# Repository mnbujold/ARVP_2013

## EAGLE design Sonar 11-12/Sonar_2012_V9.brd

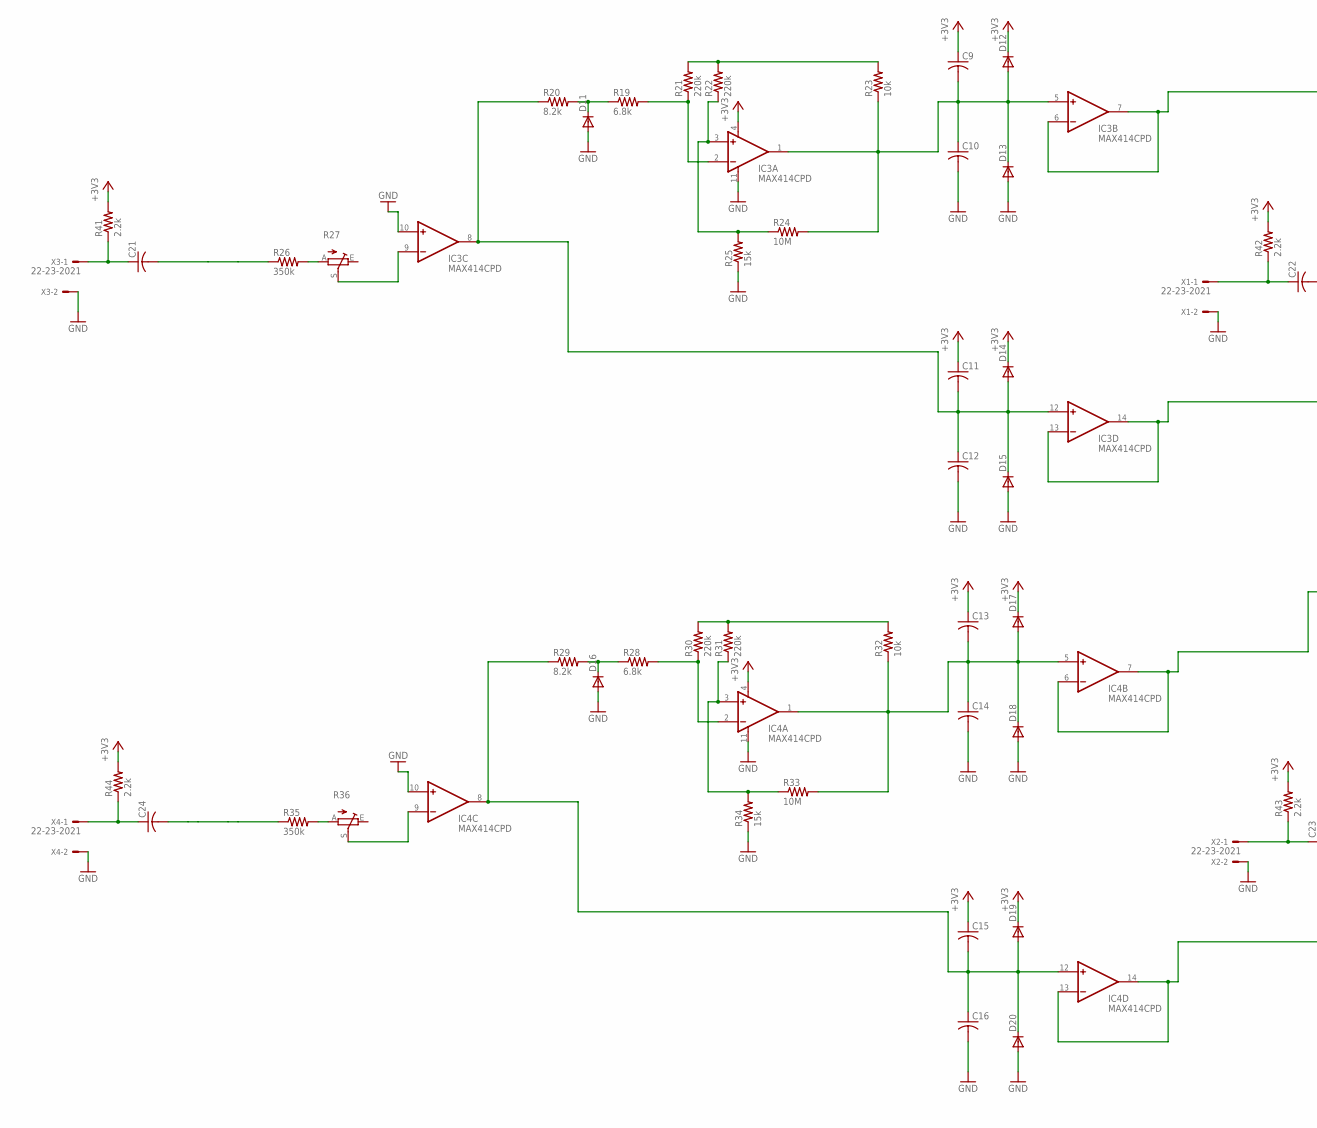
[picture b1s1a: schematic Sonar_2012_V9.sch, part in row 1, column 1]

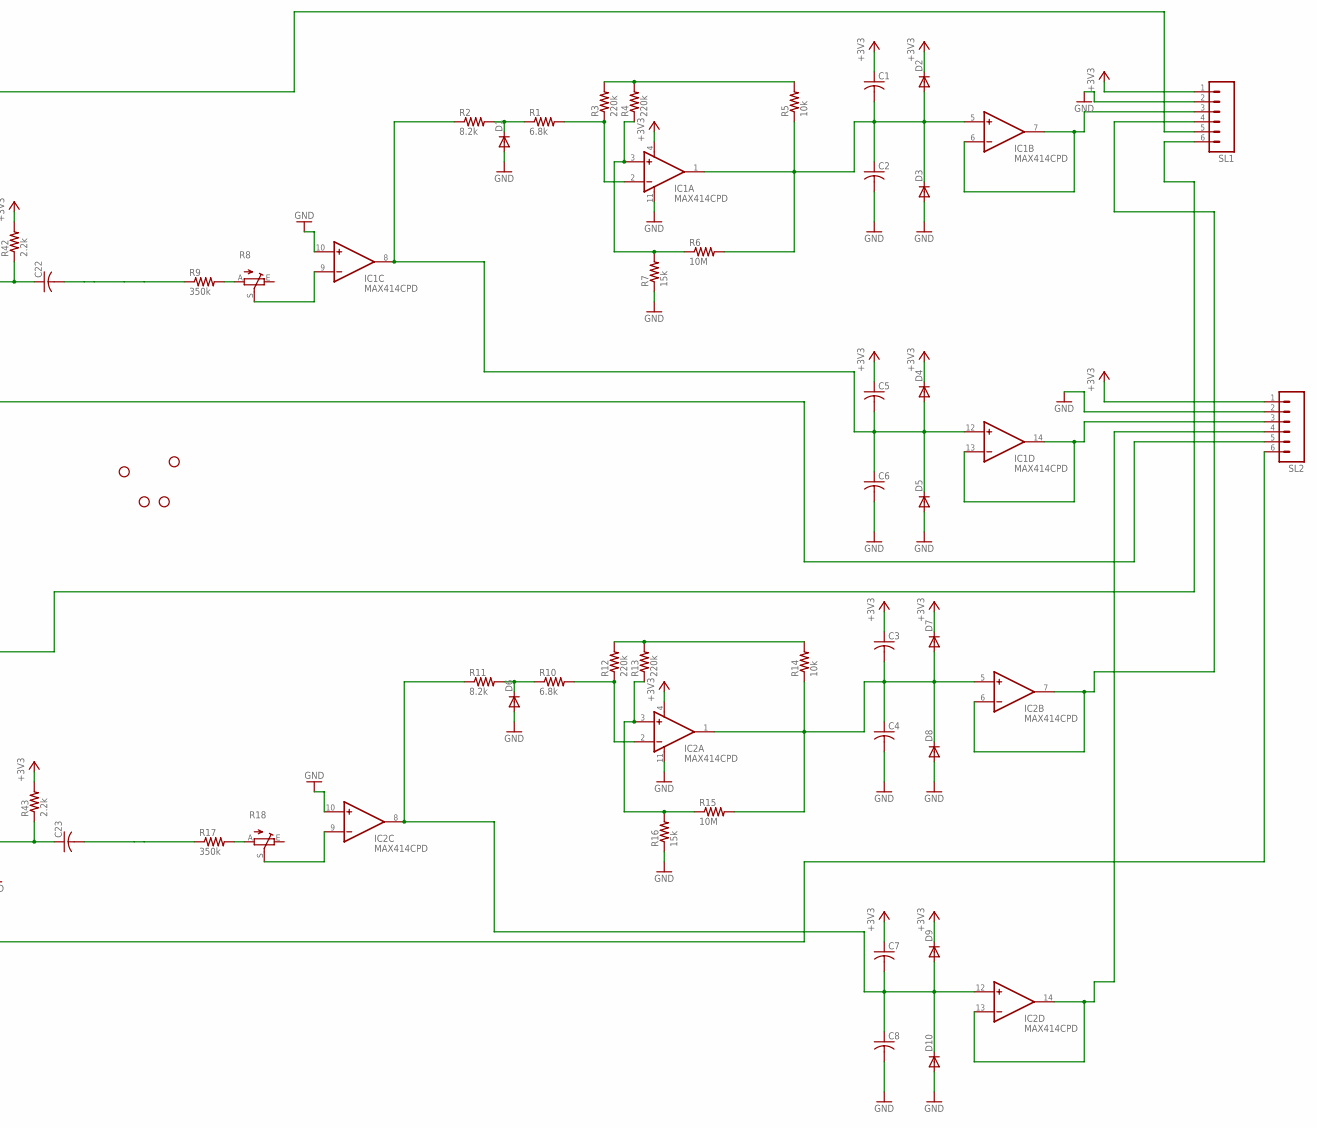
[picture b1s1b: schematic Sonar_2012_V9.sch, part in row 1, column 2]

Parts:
C1, C2, C3, C4, C5, C6, C7, C8, C9, C10, C11, C12, C13, C14, C15, C16, C21, C22, C23, C24: C-USC0603; C0603
D1, D2, D3, D4, D5, D6, D7, D8, D9, D10, D11, D12, D13, D14, D15, D16, D17, D18, D19, D20: DIODE-SOD523; SOD523
IC1, IC2, IC3, IC4: MAX414CPD; DIL14
JP1, JP2, JP3, JP4: STAND-OFF
R1, R10, R19, R28: 6.8k; M1206
R2, R11, R20, R29: 8.2k; M1206
R3, R4, R12, R13, R21, R22, R30, R31: 220k; M1206
R5, R14, R23, R32: 10k; M1206
R6, R15, R24, R33: 10M; M1206
R7, R16, R25, R34: 15k; M1206
R8, R18, R27, R36: TRIM_EU-B64Y; B64Y
R9, R17, R26, R35: 350k; M1206
R41, R42, R43, R44: 2.2k; M1206
SL1, SL2: M06; 06P
X1, X2, X3, X4: 22-23-2021

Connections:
+3V3: C1.1, C3.1, C5.1, C7.1, C9.1, C11.1, C13.1, C15.1, D2.C, D4.C, D7.C, D9.C, D12.C, D14.C, D17.C, D19.C, IC1.4 (V+), IC2.4 (V+), IC3.4 (V+), IC4.4 (V+), R41.2, R42.2, R43.2, R44.2, SL1.1, SL2.1
GND: C2.2, C4.2, C6.2, C8.2, C10.2, C12.2, C14.2, C16.2, D1.A, D3.A, D5.A, D6.A, D8.A, D10.A, D11.A, D13.A, D15.A, D16.A, D18.A, D20.A, IC1.10 (+IN), IC1.11 (V-), IC2.10 (+IN), IC2.11 (V-), IC3.10 (+IN), IC3.11 (V-), IC4.10 (+IN), IC4.11 (V-), R7.1, R16.1, R25.1, R34.1, SL1.2, SL2.2, X1.2, X2.2, X3.2, X4.2
unnamed: D1.C, R1.1, R2.2
unnamed: IC1.2 (-IN), R1.2, R3.1
unnamed: R3.2, R4.2, R5.2
unnamed: IC1.3 (+IN), R4.1, R6.1, R7.2
unnamed: C1.2, C2.1, D2.A, D3.C, IC1.1 (OUT), IC1.5 (+IN), R5.1, R6.2
unnamed: IC2.2 (-IN), R10.2, R12.1
unnamed: R12.2, R13.2, R14.2
unnamed: IC1.6 (-IN), IC1.7 (OUT), SL1.3
unnamed: D6.C, R10.1, R11.2
unnamed: IC1.9 (-IN), R8.S
unnamed: C3.2, C4.1, D7.A, D8.C, IC2.1 (OUT), IC2.5 (+IN), R14.1, R15.2
unnamed: IC1.13 (-IN), IC1.14 (OUT), SL2.3
unnamed: IC2.6 (-IN), IC2.7 (OUT), SL1.4
unnamed: C22.2, R9.1
unnamed: R8.A, R9.2
unnamed: IC2.13 (-IN), IC2.14 (OUT), SL2.4
unnamed: C5.2, C6.1, D4.A, D5.C, IC1.8 (OUT), IC1.12 (+IN), R2.1
unnamed: IC2.9 (-IN), R18.S
unnamed: C23.1, R43.1, X2.1
unnamed: R17.2, R18.A
unnamed: C7.2, C8.1, D9.A, D10.C, IC2.8 (OUT), IC2.12 (+IN), R11.1
unnamed: IC2.3 (+IN), R13.1, R15.1, R16.2
unnamed: IC3.2 (-IN), R19.2, R21.1
unnamed: R21.2, R22.2, R23.2
unnamed: D11.C, R19.1, R20.2
unnamed: C9.2, C10.1, D12.A, D13.C, IC3.1 (OUT), IC3.5 (+IN), R23.1, R24.2
unnamed: IC3.6 (-IN), IC3.7 (OUT), SL1.5
unnamed: IC3.13 (-IN), IC3.14 (OUT), SL2.5
unnamed: IC3.9 (-IN), R27.S
unnamed: C21.1, R41.1, X3.1
unnamed: R26.2, R27.A
unnamed: C11.2, C12.1, D14.A, D15.C, IC3.8 (OUT), IC3.12 (+IN), R20.1
unnamed: IC3.3 (+IN), R22.1, R24.1, R25.2
unnamed: IC4.2 (-IN), R28.2, R30.1
unnamed: R30.2, R31.2, R32.2
unnamed: D16.C, R28.1, R29.2
unnamed: C13.2, C14.1, D17.A, D18.C, IC4.1 (OUT), IC4.5 (+IN), R32.1, R33.2
unnamed: IC4.6 (-IN), IC4.7 (OUT), SL1.6
unnamed: IC4.13 (-IN), IC4.14 (OUT), SL2.6
unnamed: IC4.9 (-IN), R36.S
unnamed: C24.1, R44.1, X4.1
unnamed: R35.2, R36.A
unnamed: C15.2, C16.1, D19.A, D20.C, IC4.8 (OUT), IC4.12 (+IN), R29.1
unnamed: IC4.3 (+IN), R31.1, R33.1, R34.2
unnamed: C21.2, R26.1
unnamed: C22.1, R42.1, X1.1
unnamed: C23.2, R17.1
unnamed: C24.2, R35.1

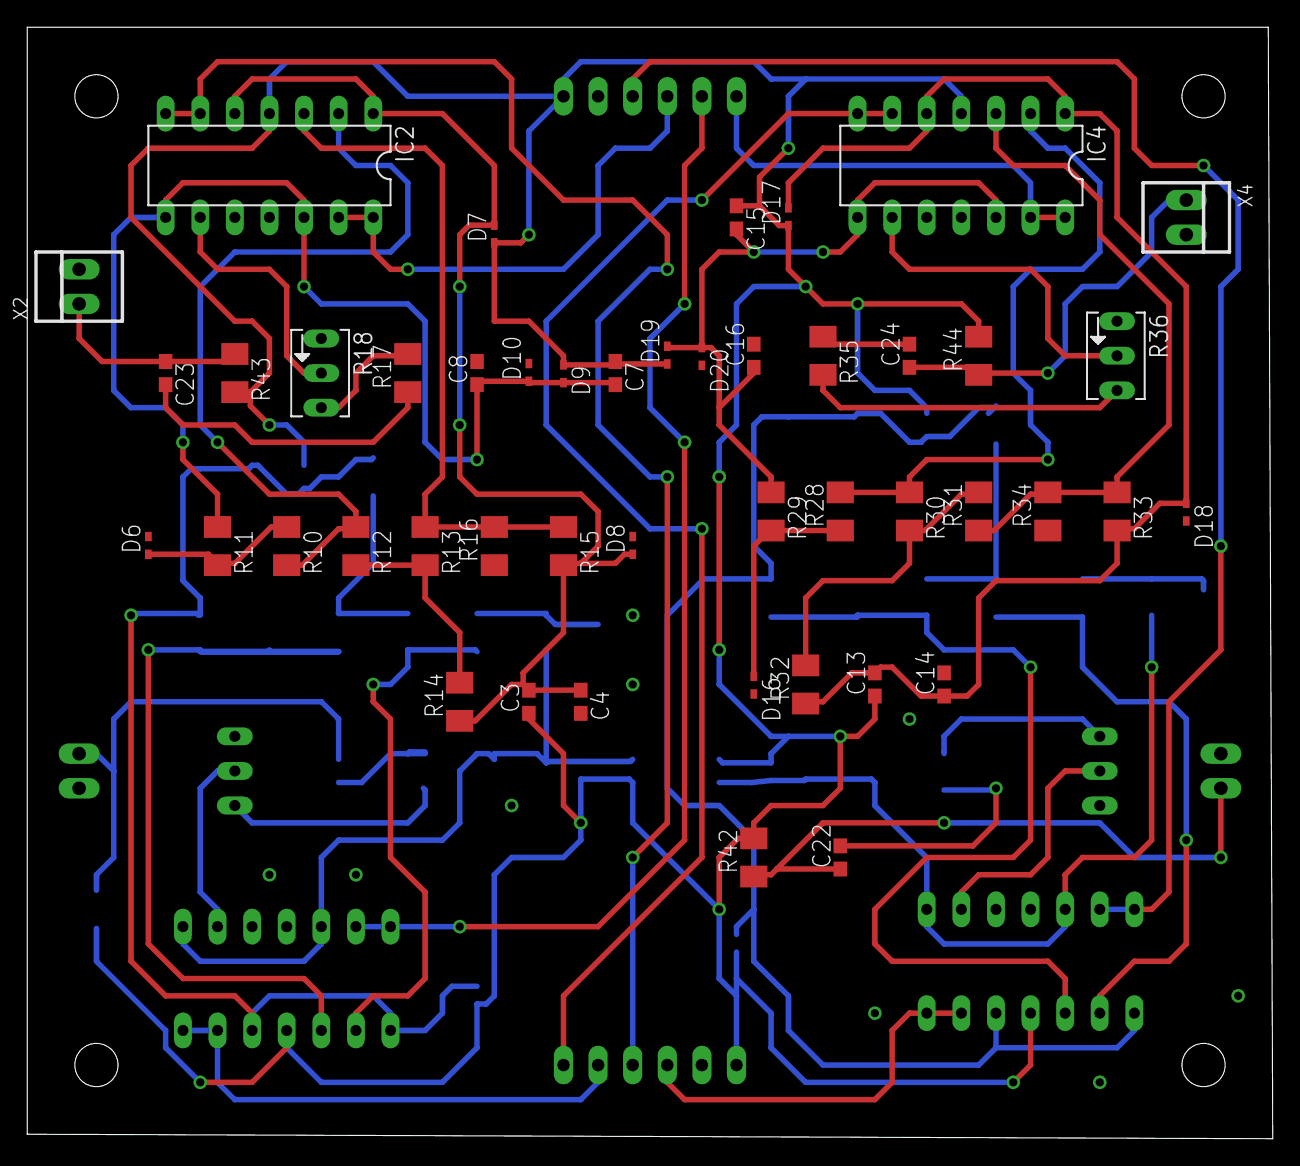
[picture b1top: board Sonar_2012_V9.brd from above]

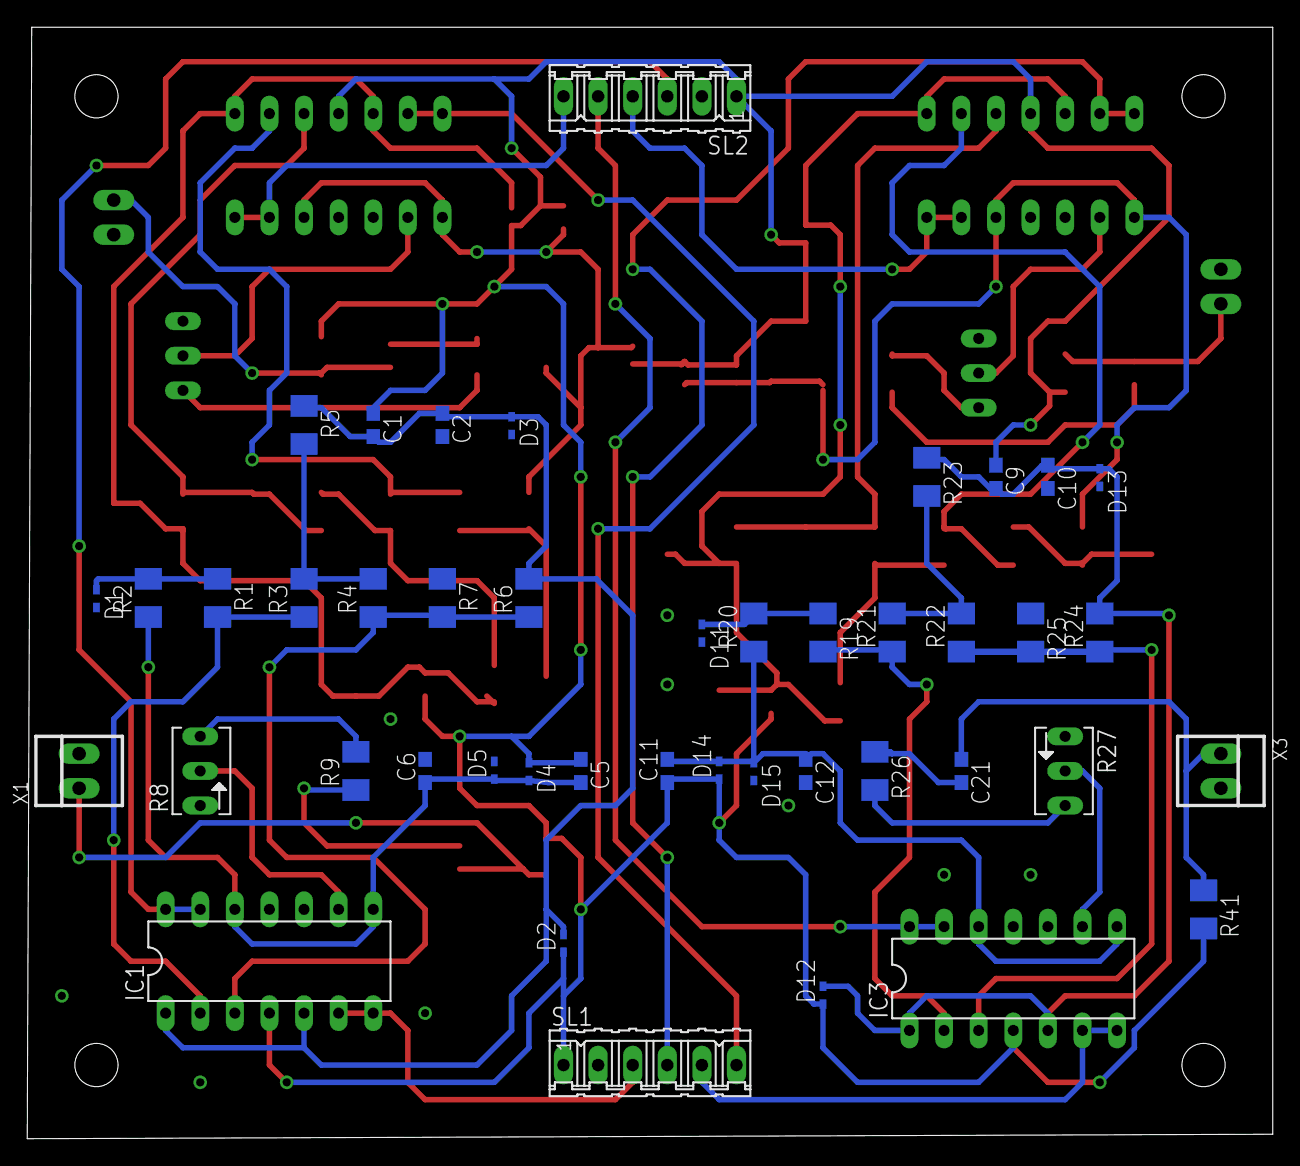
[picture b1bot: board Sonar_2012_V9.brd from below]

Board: 2 copper layers, 91.4 x 81.6 mm, 94 parts (44 on the bottom side), 50 nets.
